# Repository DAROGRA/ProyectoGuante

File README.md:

# ProyectoGuante
Diseño PCB para guante LSC

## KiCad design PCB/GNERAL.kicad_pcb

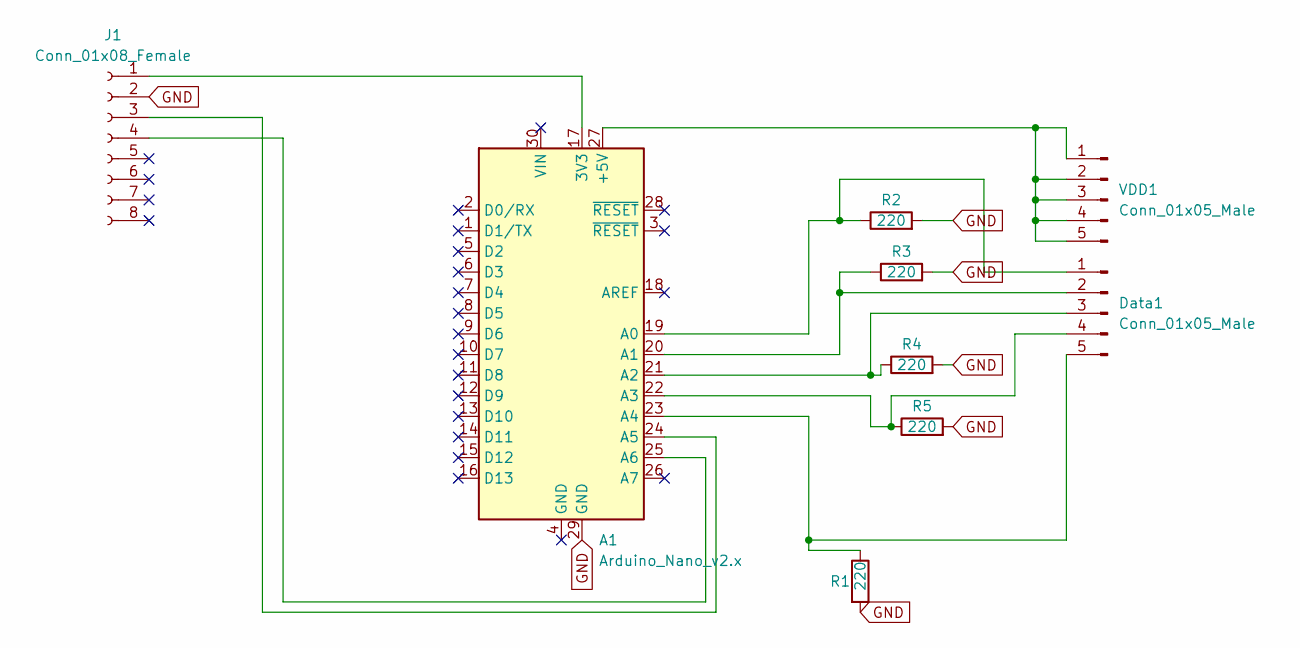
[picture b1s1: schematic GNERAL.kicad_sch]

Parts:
A1: Arduino_Nano_v2.x; Arduino_Nano
Data1: Conn_01x05_Male; JST_XH_S5B-XH-A-1_1x05_P2.50mm_Horizontal
J1: Conn_01x08_Female; PinSocket_1x08_P2.54mm_Vertical
R1, R2, R3, R4, R5: 220; R_0805_2012Metric_Pad1.20x1.40mm_HandSolder
VDD1: Conn_01x05_Male; JST_XH_S5B-XH-A-1_1x05_P2.50mm_Horizontal

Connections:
GND: A1.29 (GND), J1.2, R1.2, R2.2, R3.2, R4.2, R5.2
unnamed: A1.17 (3V3), J1.1
unnamed: A1.19 (A0), Data1.1, R2.1
unnamed: A1.20 (A1), Data1.2, R3.1
unnamed: A1.21 (A2), Data1.3, R4.1
unnamed: A1.22 (A3), Data1.4, R5.1
unnamed: A1.23 (A4), Data1.5, R1.1
unnamed: A1.24 (A5), J1.3
unnamed: A1.25 (A6), J1.4
unnamed: A1.27 (+5V), VDD1.1, VDD1.2, VDD1.3, VDD1.4, VDD1.5

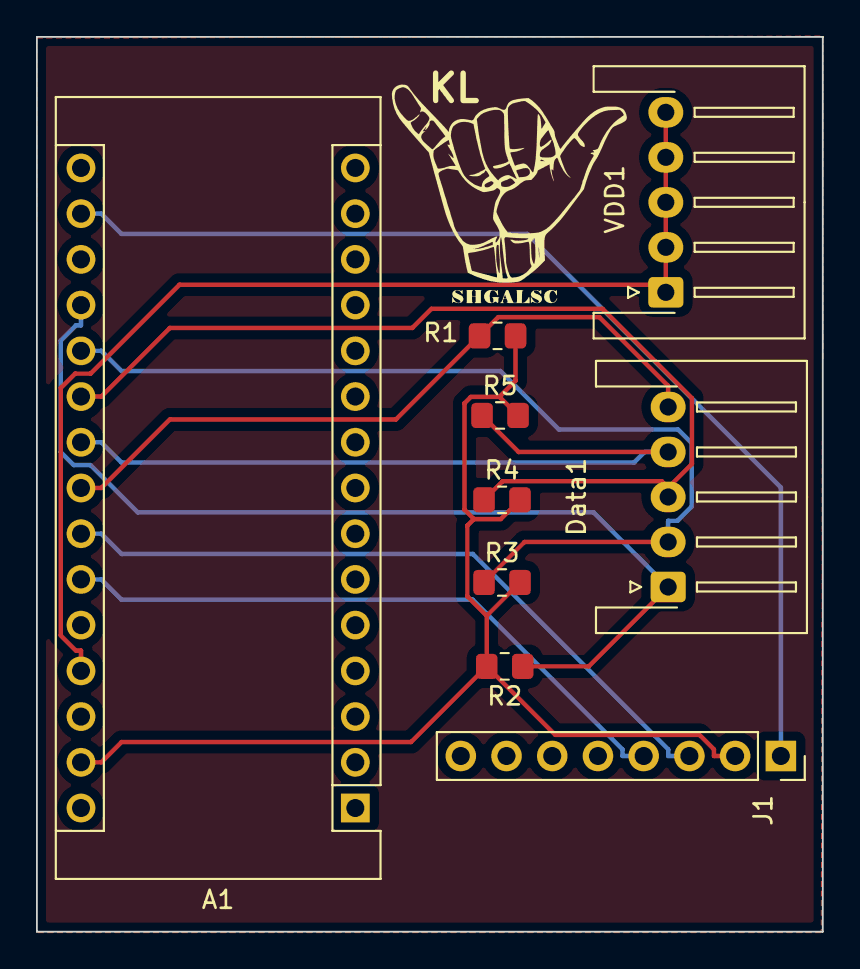
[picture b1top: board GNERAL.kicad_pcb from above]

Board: 2 copper layers, 43.7 x 49.7 mm, 10 parts (0 on the bottom side), 10 nets.

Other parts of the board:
KL: LOGO; logod

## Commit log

2023-03-11 INCIO DEL CAOS
2023-03-11 medio
2023-03-11 hola
2023-03-11 requieroruteo
2023-03-11 Work
2023-03-11 me canseee
2023-03-11 AhoraSi
2023-03-11 FNIAL
2023-06-07 Arduino
2023-06-14 nuevo
2023-06-14 orden
2023-06-19 DATOS
2023-06-21 Actualizacion
    mas documentos añadidos
